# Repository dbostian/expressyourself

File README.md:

# express yourself

A DIY triple expression pedal. This pedal was heavily inspired by the Old Blood Noise Endeavors Expression Ramper x3. I wanted to add the ability for the pedal to modulate its own values. It has three expression outputs that can sync with each other, and affect each other in weird ways.

This project is work in progress, and is released on an as-is basis. This repository contains all code, artwork (I printed a vinyl sticker), pcb schematics, gerbers, a bom, as well as 3d printing files (stls, f3d, step) for a 3d printed enclosure. The pedal will fit in a 125b enclosure. The code is working as described below/shown in the videos, but is in a preliminary stage and may contain bugs. In short, use at your own risk.

I am not planning to release detailed build instructions, but if you're a steady hand at soldering, have built a few diy pedals before, ordered custom pcbs, sourced a bom, and have flashed an arduino or two, you should be able to handle this.

Overview Video: https://www.youtube.com/watch?v=8aHI_HfOTI8
Followup Video: https://www.youtube.com/watch?v=umGa9XkKtoM
Part 3: https://www.youtube.com/watch?v=ajVojKqwqVI

## basic usage

The pedal has three sets of expression controls, arranged in columns from left to right. For any exp, you can set the wave **shape** (triangle, square or sine), an **a** value and a **b** value, and a **rate**. The exp will oscillate between **a** and **b** at the **rate** you set, using the selected **shape**. All knob settings are relative - the knob may not match the value when changing the **set** switch, so turning the knob will raise or lower the value accordingly. Pay attention to the LED's brightness, as it reflects the actual value.

Exp 1 can also have its **rate** determined by tap tempo. At most, the last five taps will be used.

To enable an exp's jack, tap the footswitch to enable it. The LED will turn white. Tap again to turn it off. The output of a jack is:
* A if the set switch is on **a**
* B if the set switch is on **b**
* Oscillating if the set switch is on **rate** and the exp is **on**
* A if the set switch is on **rate** and the exp is **off**

You can sync exp2 and exp3 the exp to their left. If **sync** is set to **rate**, the **rate** value will be copied over. If set to **all**, the **a** and **b** values will be copied as well. When syncing (**rate** or **all**), changing the **rate** value will adjust the local rate in multiples of the exp to the left - 1/8, 1/4, 1/2, 1x, 2x, 3x, or 4x.

If you hold down any footswitch while changing the **sync** switch, the exp will enter **mod** mode. The output of the exp to the left will control an aspect of this exp. as follows:
* In **amp** mod mode, the amplitude of the wave will be changed by the output of the exp to the left. **a** and **b** will move apart or closer together about their midpoint. 0% touching, 50% original values, 100% twice as far apart.
* In **freq** mod mode, the frequency of the wave will be changed. The **rate** value will be replaced with the output of exp to the left.
* In **phase** mod mode, the phase of the wave will be offset by the value of the exp to the left. 0%: minus one half wavelength, 50%: no change, 100%: plus one half wavelength.

In **amp** mod mode, the value may exceed the maximum or minimum value of the pedal. In this case, **wavefolding** will occur.

Changing the **sync** switch without holding a footswitch down will turn off the **mod** mode. You can have **sync** mode and **mod** mode active at the same time: move the **sync** switch to the desired **sync** mode, hold the foot switch and select the desired **mod** mode. You cannot have more than one **sync** mode or **mod** mode active at the same time.

If you change the **shape** switch while holding a foot switch, you will enter **random** mode - each time the wave completes a cycle, random values for **a** and **b** will be chosen, using values between the original **a** and **b**.

Future features and code changes:
* One-shot mode. Holding the tap tempo button while selecting shape will put it into one-shot mode. The EXP will move from A to B when the footswitch is tapped, and back from B to A again when tapped again, and so on.
* Hold to pause. While a footswitch is held, the exp's output and progress will be paused. It will resume when the footswitch is released.
* USB Midi?

## design notes

The schematic and pcb were layed out in KiCad 10.

This circuit uses every IO pin available on the Arduino Pro Micro. To reduce the number of pins used for the switches (many of which have three positions), I used a key matrix with diodes arranged in a 4 x 5 grid. This reduced the pins needed to 9. This is very similar to how a computer keyboard works. For each three-way switch, I can check two positions, and if neither is "pressed," I can tell that it is in the middle position. I'm using the Adafruit_Keypad library for this. They switch matrix handles all of the toggle switches and the momentaries (tap tempo, plus the foot switches). For more information on how a key matrix works (and why this pedal needs so many diodes), check out this article: https://www.dribin.org/dave/keyboard/one_html/

The digipots are controlled using a software SPI. In using every pin available, I ended up using the MISO pin as one of the CS lines. The built in SPI library conflicted with that use case, hence the bit-banging solution.

The artwork is based on a photo of a cloud that I took, converted to halftones. This is color shifted using a CMYK color scheme for the three expression units. I created the art in InkScape.

The 3d print files were for testing hole location, prior to drilling into metal. I've included them for reference. These were designed in Autodesk Fusion.

The code was written in the Arduino IDE. AI use in this project is limited to GitHub copilot commit messages from editing this README file - not for code generation, pcb design, art, or anything else. It certainly didn't help with soldering.

## build notes

The expressionx3.csv contains a fairly complete parts list. Pay attention to the csv, not what is in KiCad.

* Knobs are 20mm apart. I used 19mm diameter Davies style knobs.
* JST connectors did not fit - ignore bom and just use pin header.
* TRS jack choice is important. Others did not fit in the enclosure.
* The pcb is challenging to solder, as I completely disregarded courtyards during design. Plan ahead while soldering. Paying for assembly probably won't work without some updates.
* I installed the pro micro using pin header for clearance. You may want to drill a hole/mill a slot in the side of the enclosure for easy usb cable access, especially if you are planning on experimenting with your own code.
* You may need to bend some terminals during assembly to get everything to fit inside. I needed this for the foot switches.
* You might need to use other sized digipots from the MCP41xx series (bigger/smaller than 50k), depending on what you are plugging them into.
* Someone suggested I flip the outer two foot switches around to make it possible to hit the center switch with normal sized toes.

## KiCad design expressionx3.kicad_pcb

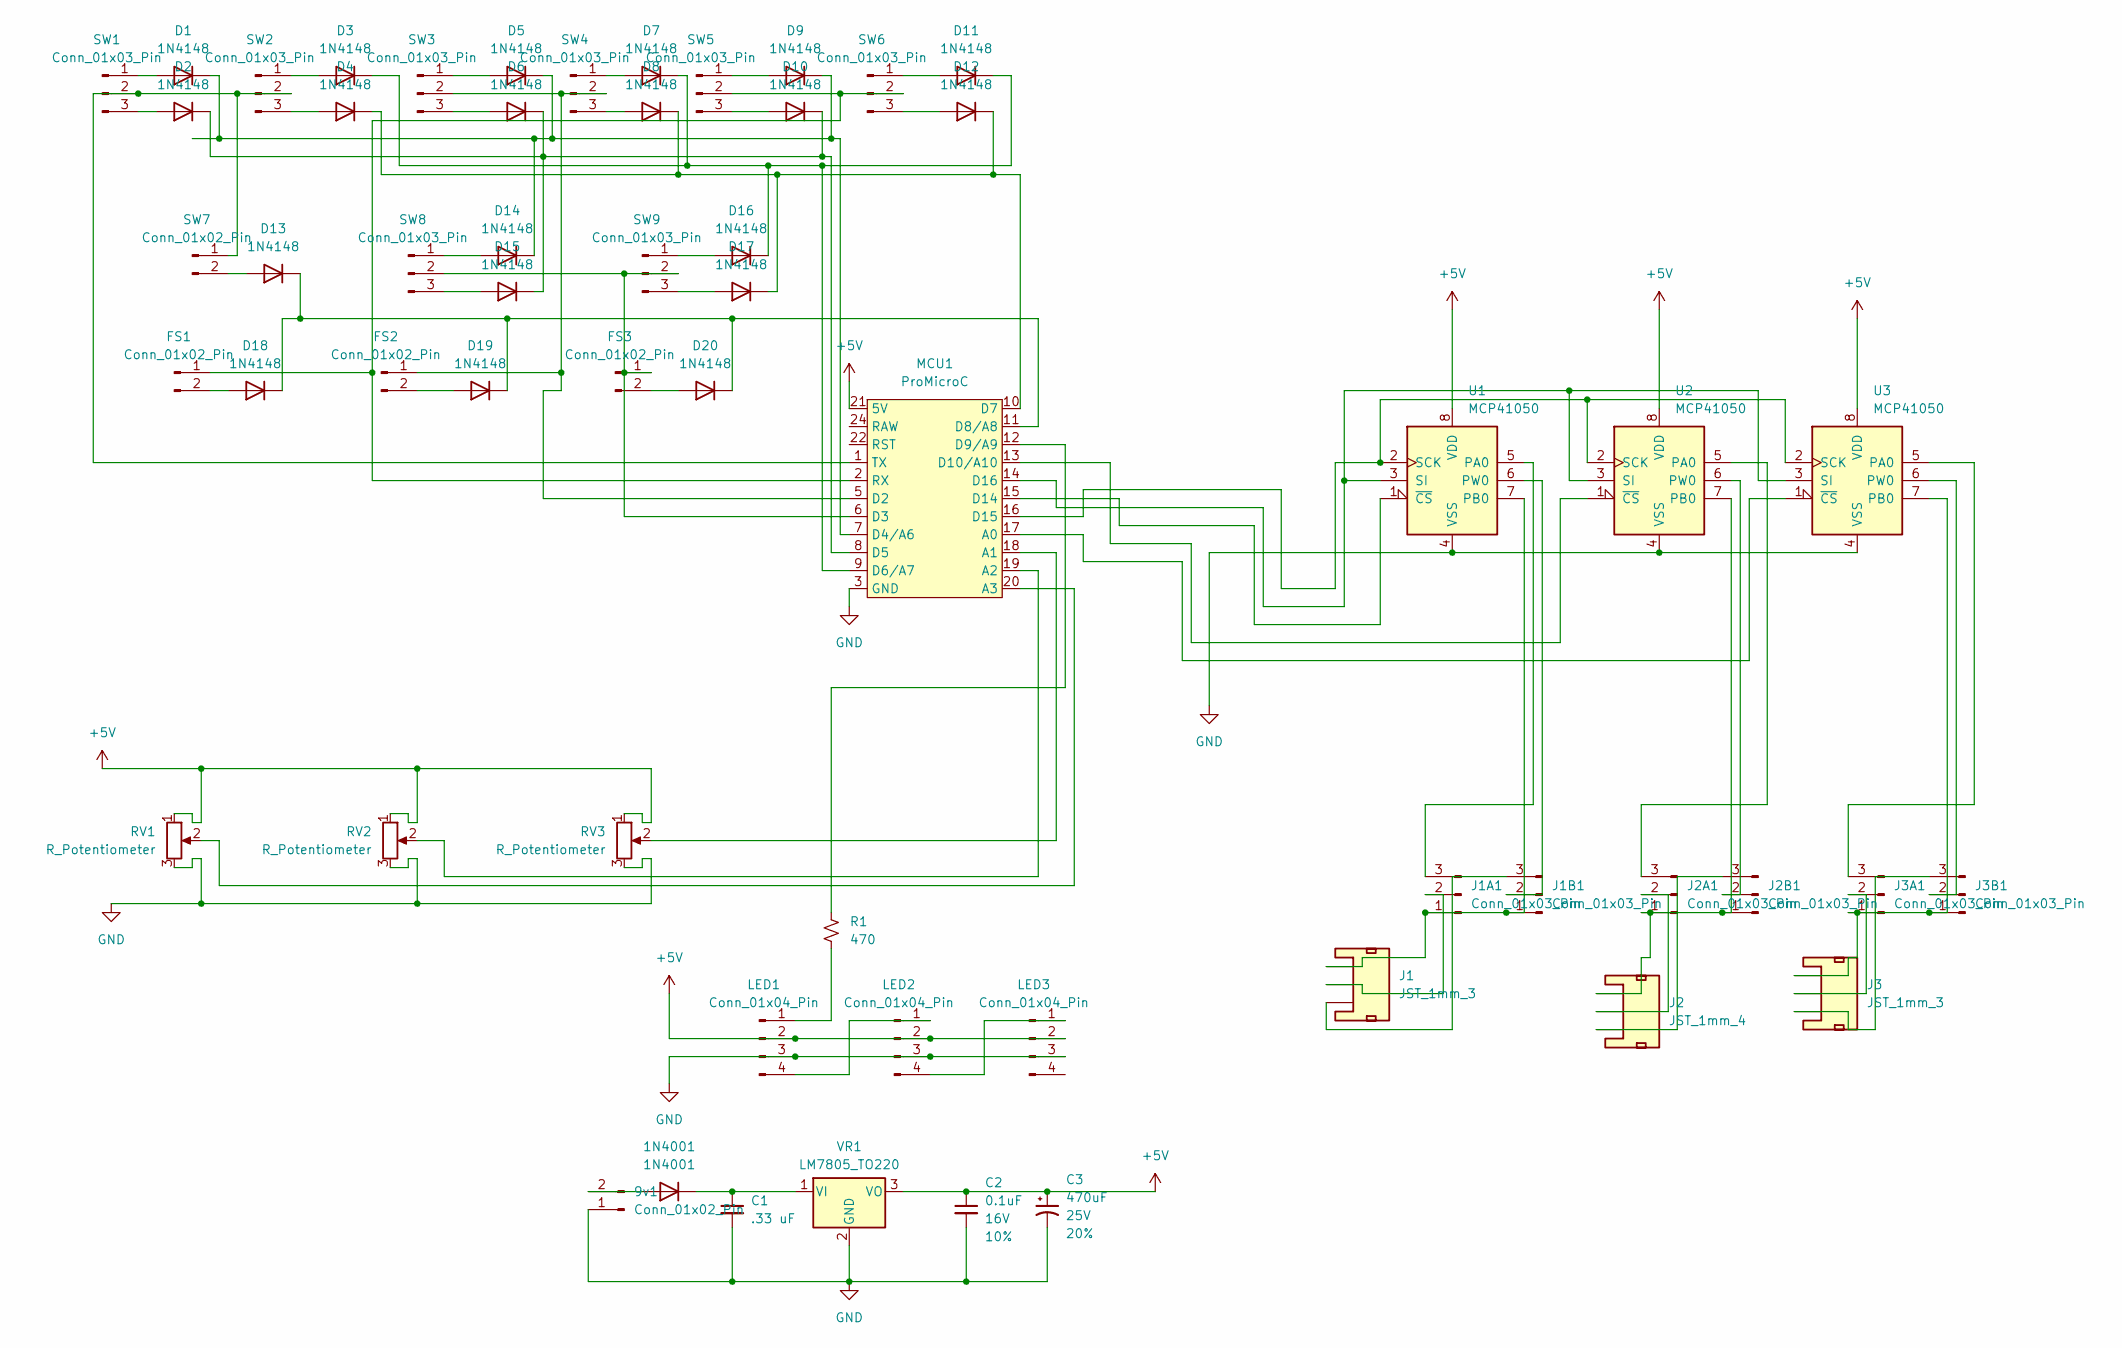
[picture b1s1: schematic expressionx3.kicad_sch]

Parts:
1N4001: 1N4001; D_DO-41_SOD81_P10.16mm_Horizontal
9v1: Conn_01x02_Pin; PinHeader_1x02_P2.54mm_Vertical
C1: .33 uF; C_Disc_D10.0mm_W2.5mm_P5.00mm
C2: 0.1uF; C_Disc_D10.0mm_W2.5mm_P5.00mm; Voltage 16V; Tolerance 10%
C3: 470uF; CP_Radial_D8.0mm_P3.50mm; Voltage 25V; Tolerance 20%
D1, D2, D3, D4, D5, D6, D7, D8, D9, D10, D11, D12, D13, D14, D15, D16, D17, D18, D19, D20: 1N4148; D_DO-35_SOD27_P7.62mm_Horizontal
FS1, FS2, FS3: Conn_01x02_Pin; PinHeader_1x02_P2.54mm_Vertical
J1, J3: JST_1mm_3; JST_XH_B3B-XH-A_1x03_P2.50mm_Vertical
J1A1, J1B1, J2A1, J2B1, J3A1, J3B1: Conn_01x03_Pin; PinHeader_1x03_P2.54mm_Vertical
J2: JST_1mm_4; JST_XH_B3B-XH-A_1x03_P2.50mm_Vertical
LED1, LED2, LED3: Conn_01x04_Pin; PinHeader_1x04_P2.54mm_Vertical
MCU1: ProMicroC; Sparkfun_Pro_Micro
R1: 470; R_Axial_DIN0204_L3.6mm_D1.6mm_P7.62mm_Horizontal
RV1, RV2, RV3: R_Potentiometer; Potentiometer_Piher_T-16L_Single_Vertical_Hole
SW1, SW2, SW3, SW4, SW5, SW6, SW8, SW9: Conn_01x03_Pin; SPDT
SW7: Conn_01x02_Pin; SPST
U1, U2, U3: MCP41050; DIP-8_W7.62mm
VR1: LM7805_TO220; TO-220-3_Vertical

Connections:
+5V: C2.1, C3.1, LED1.2, LED2.2, LED3.2, MCU1.21 (5V), RV1.1, RV2.1, RV3.1, U1.8 (VDD), U2.8 (VDD), U3.8 (VDD), VR1.3 (VO)
GND: 9v1.1, C1.2, C2.2, C3.2, LED1.3, LED2.3, LED3.3, MCU1.3 (GND), MCU1.4 (GND), MCU1.23 (GND), RV1.3, RV2.3, RV3.3, U1.4 (VSS), U2.4 (VSS), U3.4 (VSS), VR1.2 (GND)
unnamed: 1N4001.2 (A), 9v1.2
unnamed: 1N4001.1 (K), C1.1, VR1.1 (VI)
unnamed: D1.2 (A), SW1.1
unnamed: D1.1 (K), D5.1 (K), D9.1 (K), D14.1 (K), MCU1.7 (D4/A6)
unnamed: D2.2 (A), SW1.3
unnamed: D3.2 (A), SW2.1
unnamed: D4.2 (A), SW2.3
unnamed: D5.2 (A), SW3.1
unnamed: D6.2 (A), SW3.3
unnamed: D7.2 (A), SW4.1
unnamed: D8.2 (A), SW4.3
unnamed: D9.2 (A), SW5.1
unnamed: D10.2 (A), SW5.3
unnamed: D2.1 (K), D6.1 (K), D10.1 (K), D15.1 (K), MCU1.8 (D5)
unnamed: D11.2 (A), SW6.1
unnamed: D3.1 (K), D7.1 (K), D11.1 (K), D16.1 (K), MCU1.9 (D6/A7)
unnamed: D12.2 (A), SW6.3
unnamed: D4.1 (K), D8.1 (K), D12.1 (K), D17.1 (K), MCU1.10 (D7)
unnamed: D13.2 (A), SW7.2
unnamed: D13.1 (K), D18.1 (K), D19.1 (K), D20.1 (K), MCU1.11 (D8/A8)
unnamed: D14.2 (A), SW8.1
unnamed: D15.2 (A), SW8.3
unnamed: D16.2 (A), SW9.1
unnamed: D17.2 (A), SW9.3
unnamed: D18.2 (A), FS1.2
unnamed: D19.2 (A), FS2.2
unnamed: D20.2 (A), FS3.2
unnamed: FS1.1, MCU1.2 (RX), SW5.2, SW6.2
unnamed: FS2.1, MCU1.5 (D2), SW3.2, SW4.2
unnamed: FS3.1, MCU1.6 (D3), SW8.2, SW9.2
unnamed: J1.1, J1A1.1, J1B1.1, U1.7 (PB0)
unnamed: J1.2, J1A1.2
unnamed: J1A1.3, U1.5 (PA0)
unnamed: J1B1.2, U1.6 (PW0)
unnamed: J1.3, J1B1.3
unnamed: J2.1, J2A1.1, J2B1.1, U2.7 (PB0)
unnamed: J2.2, J2A1.2
unnamed: J2A1.3, U2.5 (PA0)
unnamed: J2B1.2, U2.6 (PW0)
unnamed: J2.3, J2B1.3
unnamed: J3.1, J3A1.1, J3B1.1, U3.7 (PB0)
unnamed: J3.2, J3A1.2
unnamed: J3A1.3, U3.5 (PA0)
unnamed: J3B1.2, U3.6 (PW0)
unnamed: J3.3, J3B1.3
unnamed: LED1.1, R1.1
unnamed: LED1.4, LED2.1
unnamed: LED2.4, LED3.1
unnamed: MCU1.17 (A0), U3.1 (~CS)
unnamed: MCU1.18 (A1), RV3.2
unnamed: MCU1.19 (A2), RV2.2
unnamed: MCU1.20 (A3), RV1.2
unnamed: MCU1.12 (D9/A9), R1.2
unnamed: MCU1.13 (D10/A10), U2.1 (~CS)
unnamed: MCU1.15 (D14), U1.1 (~CS)
unnamed: MCU1.16 (D15), U1.2 (SCK), U2.2 (SCK), U3.2 (SCK)
unnamed: MCU1.14 (D16), U1.3 (SI), U2.3 (SI), U3.3 (SI)
unnamed: MCU1.1 (TX), SW1.2, SW2.2, SW7.1

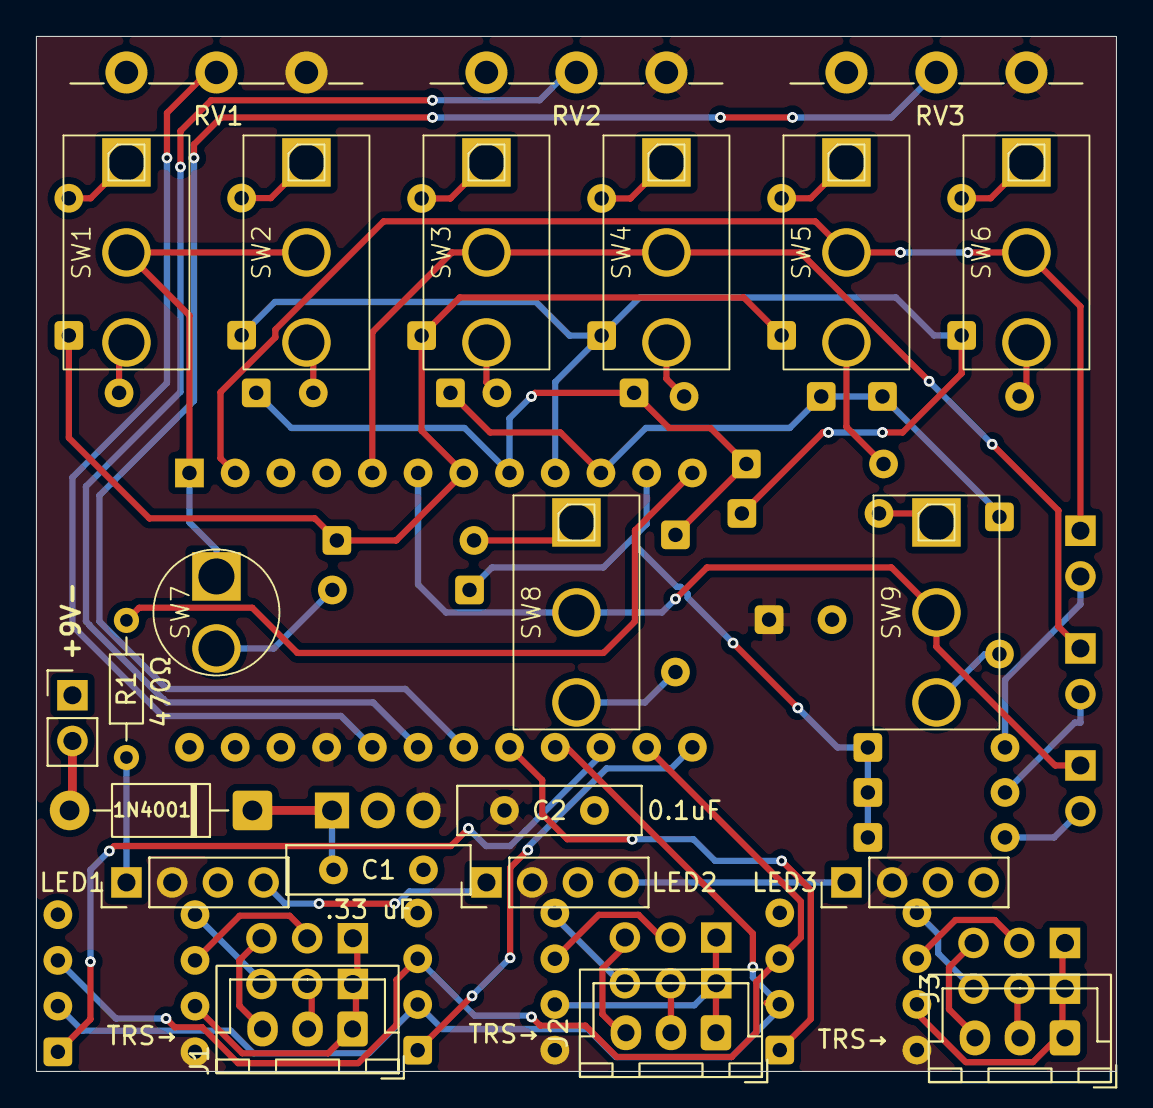
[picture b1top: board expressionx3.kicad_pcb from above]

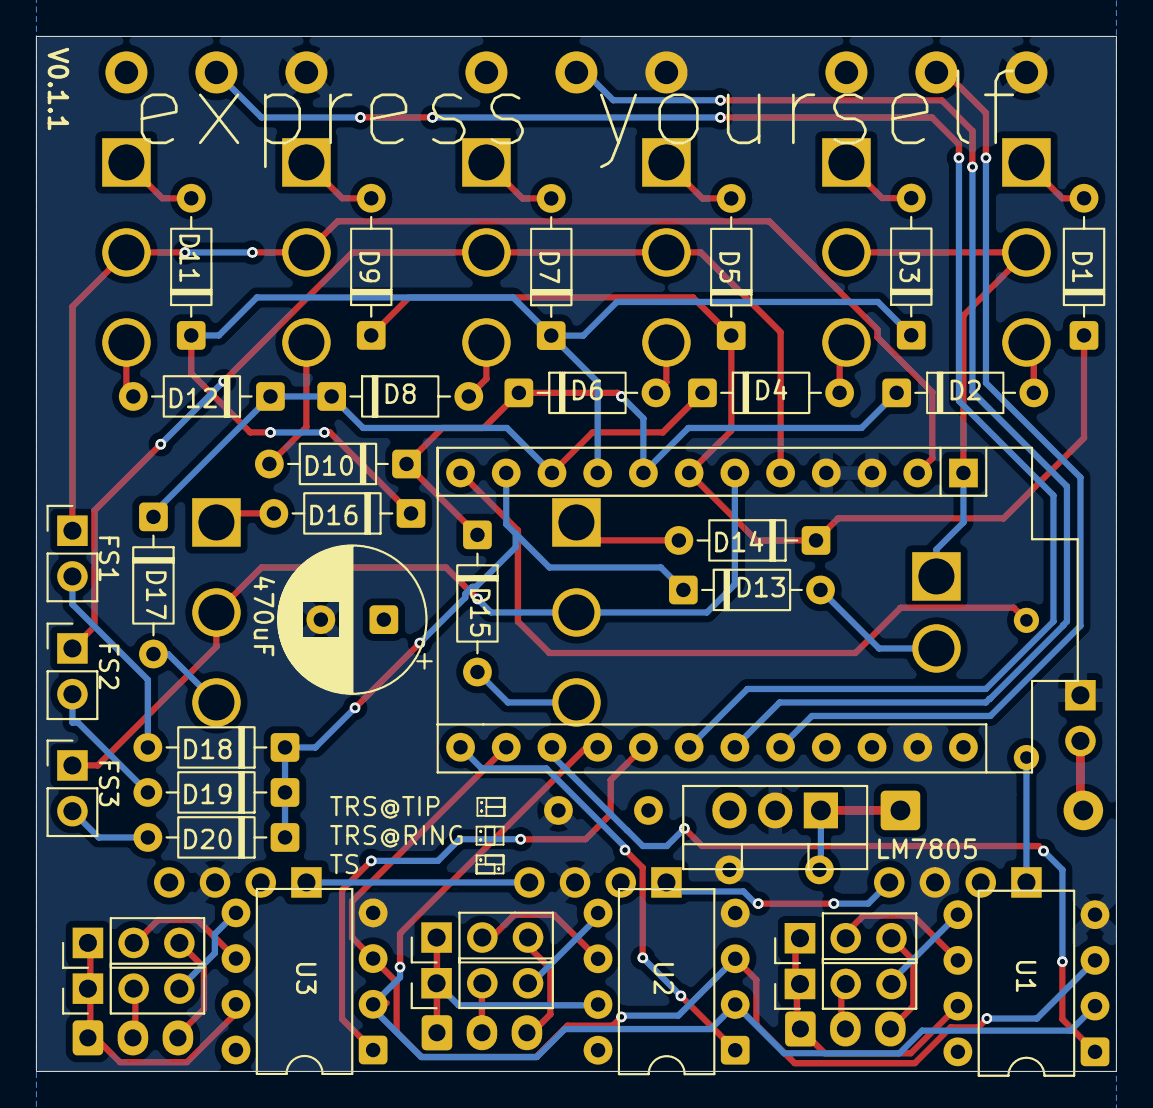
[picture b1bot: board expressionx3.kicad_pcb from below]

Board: 2 copper layers, 60.0 x 57.5 mm, 58 parts (35 on the bottom side), 60 nets.
